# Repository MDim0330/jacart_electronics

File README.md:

**JACart Electronics Repo**

Contain Python and Arduino controller code for managing the Teleop board.

**Repo Contents**

cart_teleop_dac:/ Updated Arduino teleop code that utilizes DACs instead of PWM signals. This version should be the one used going forward.

python_teleop:/ Stand-alone python controller for teleop_board

libs:/ Require libraries for operating the Arudino teleop code

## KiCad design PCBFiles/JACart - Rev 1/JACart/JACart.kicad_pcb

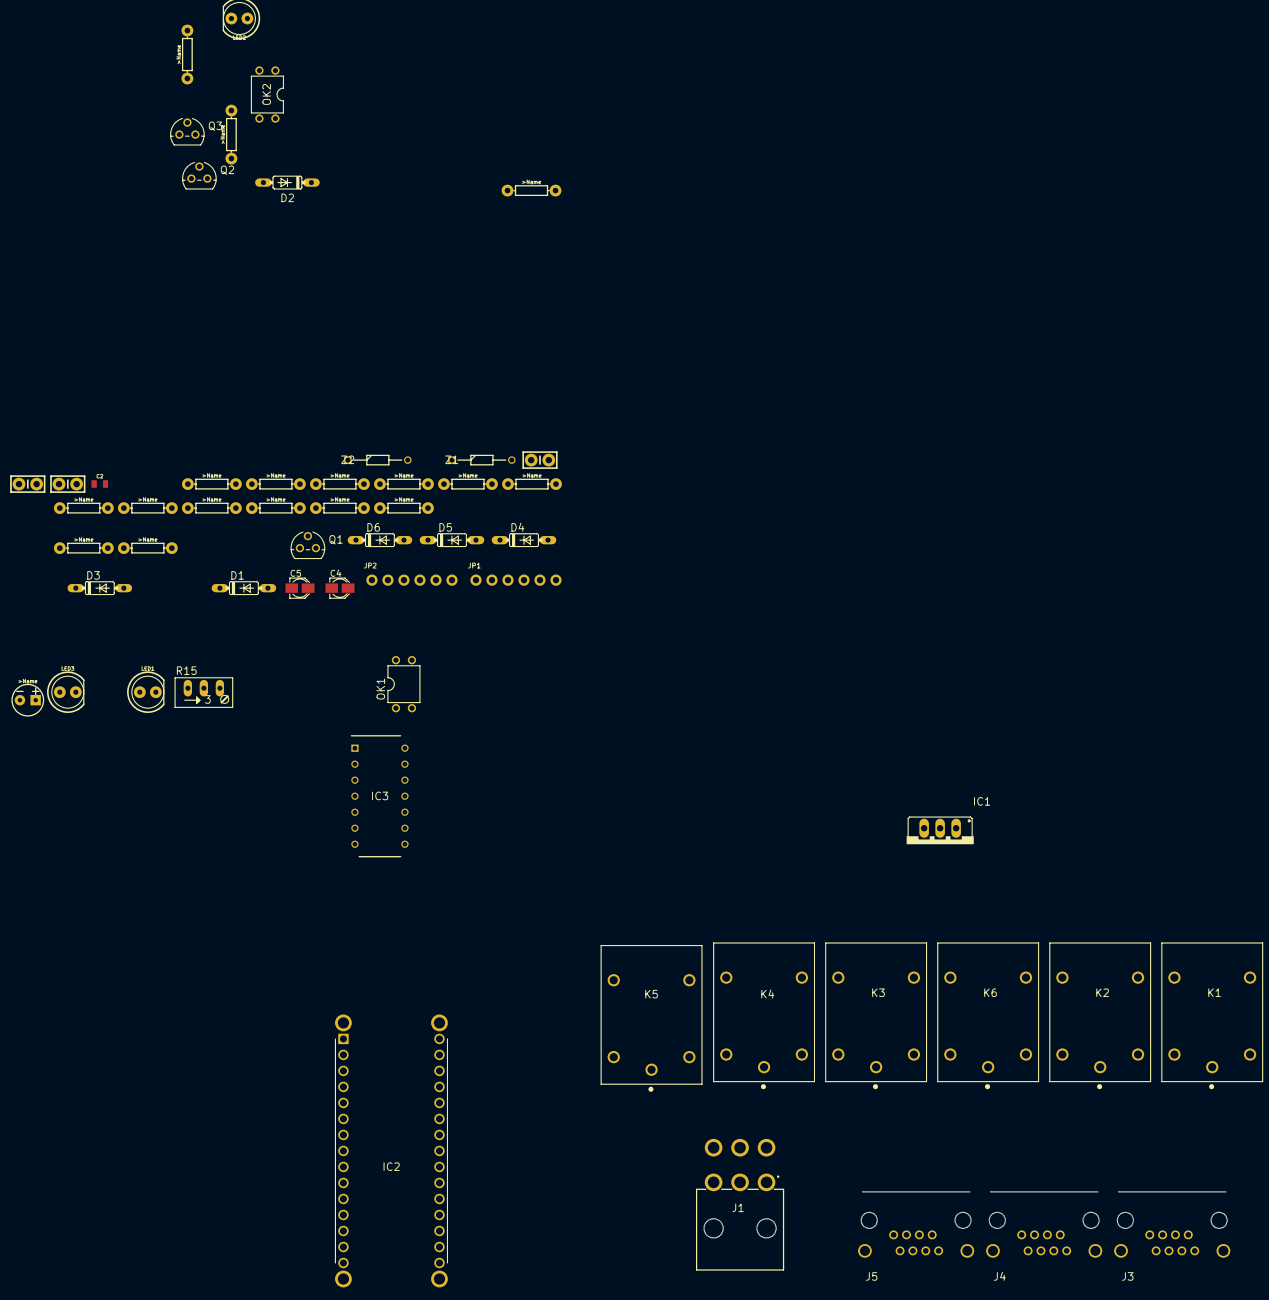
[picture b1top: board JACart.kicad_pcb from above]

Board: 2 copper layers, 56 parts (0 on the bottom side), 51 nets, no tracks yet.

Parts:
C1, C6: 0.1uF; CAP-PTH-SMALL-KIT
C2: 0.33µF; 0805
C3: 10uF; CPOL-RADIAL-2.5MM-5MM
C4, C5: 330uF; PANASONIC_A
C7: 1.0uF; CAP-PTH-SMALL-KIT
D1, D2, D3, D4, D5, D6: 1N4148; DO35-7
IC1: LM7805; 78XXS
IC2: ARD-NANO30NP; ARDNANO30NP
IC3: LMC6484IN; DIP794W56P254L1905H533Q14N
J1: 39-30-1060; 39-30-1060_1
J3: Steering; GLX-S-88M
J4: Brake; GLX-S-88M
J5: Throttle; GLX-S-88M
JP1, JP2: MCP4725; 1X06_ROUND_70
K1: Brake(1); RELAY_JS1-5V-F
K2: Brake(2); RELAY_JS1-5V-F
K3: Throttle(3); RELAY_JS1-5V-F
K4: Throttle(4); RELAY_JS1-5V-F
K5: Throttle; RELAY_JS1-5V-F
K6: Brake; RELAY_JS1-5V-F
LED1: Brake; LED_5MM
LED2: Throttle; LED_5MM
LED3: Auto; LED_5MM
OK1, OK2: PC817; DIL04
Q1, Q2, Q3: 2N3904; TO92
R1, R3: 510; AXIAL-0.3
R2, R4, R7, R9: 470; AXIAL-0.3
R5, R6, R13: 220; AXIAL-0.3
R8: 1M; AXIAL-0.3
R10: TBD; AXIAL-0.3
R11, R12, R14: 10k; AXIAL-0.3
R15: 1k; RJ9W
R16: 100; AXIAL-0.3
R17, R18: 1k; AXIAL-0.3
Z1, Z2: BAT85S-TR; DIOAD950W60L350D150

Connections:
5V: C1.1, C3.1, C6.1, D1.C, IC1.OUT, IC2.19, J1.2, J1.5, J3.2, JP1.1, JP2.1, JP2.5, K6.2, OK1.4
/AUTO: D3.C, D4.C, D5.C, D6.C, J1.3, K1.2, K2.2, K3.2, K4.2, R7.P$1
/BKA: IC2.11, R2.P$2
/BRKSIG: K1.3, Z1.1, Z2.1
/PANIC: IC3.4, J1.6, R14.P$2, R15.E, R18.P$2
/POTWPR: IC2.27, J3.1
/SCL: IC2.22, JP1.3, JP2.3
/SDA: IC2.23, JP1.4, JP2.4
/STRLFT: IC2.13, J3.8, JP2.6
/STRRT: IC2.12, J3.7, JP1.6
/TLA: IC2.10, R4.P$2
/TTLSIG: C4.+, K3.3, R5.P$1
GND: C1.2, C2.2, C3.2, C4.-, C5.-, C6.2, D3.A, D4.A, D5.A, D6.A, IC1.GND, IC2.4, IC2.17, IC3.11, J1.1, J3.3, J4.3, J5.3, JP1.2, JP2.2, K1.5, K2.5, K3.5, K4.5, LED1.K, LED2.K, LED3.K, Q1.3, Q2.3, Q3.3, R9.P$1, R13.P$1, R15.A
unnamed: C2.1, IC1.IN, J1.4
unnamed: C5.+, R6.P$1, Z1.2
unnamed: C7.1, IC3.7, Z2.2
unnamed: C7.2, R17.P$1
unnamed: D1.A, K6.5, Q1.1
unnamed: D2.A, K5.5, Q2.1
unnamed: D2.C, K5.2, OK2.4
unnamed: IC2.8, R5.P$2
unnamed: IC2.9, R6.P$2
unnamed: IC3.1, R8.P$2, R12.P$2
unnamed: IC3.2, R8.P$1, R11.P$1
unnamed: IC3.6, R10.P$1, R17.P$2
unnamed: IC3.12, R13.P$2, R14.P$1
unnamed: IC3.5, IC3.13, IC3.14, R16.P$1
unnamed: J4.2, K2.4
unnamed: J4.4, K1.4
unnamed: J4.6, K1.1
unnamed: J4.7, K6.1
unnamed: J4.8, K2.1
unnamed: J5.2, K4.4
unnamed: J5.4, K3.4
unnamed: J5.6, K3.1
unnamed: J5.7, K5.1
unnamed: J5.8, K4.1
unnamed: K2.3, K6.3
unnamed: K4.3, K5.3
unnamed: LED1.A, OK1.2
unnamed: LED2.A, OK2.2
unnamed: LED3.A, R7.P$2
unnamed: OK1.1, R2.P$1
unnamed: OK1.3, R1.P$2
unnamed: OK2.1, R4.P$1
unnamed: OK2.3, R3.P$2
unnamed: Q1.2, R1.P$1
unnamed: Q2.2, Q3.1, R3.P$1
unnamed: Q3.2, R18.P$1
unnamed: R9.P$2, R10.P$2, R12.P$1, R16.P$2
unnamed: R11.P$2, R15.S

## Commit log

2019-10-29 Add existing files
2019-11-19 v2.0
2020-06-03 commit of current arduino code
2020-08-19 fix binary format.
2020-08-19 remove some prints
2020-09-01 fix baud rate
2020-09-20 fix for python3
2020-09-20 improve reliability of serial reading
2020-09-20 fix bug
2020-10-18 add and rename teleop to this repo
2020-10-21 changed usb port to '/dev/ttyUSB9'
2020-11-05 Upload schematic of current controller board schematics
2020-11-11 new dac version
2020-11-12 Ignore my dev environment files
2020-11-12 Update comments
2020-11-12 Add libs folder to hold Arduino teleop libraries
2020-11-12 Deprecate old PWM teleop board
2020-11-17 Copy in Arduino libraries from local install
2020-11-24 Remove bad libraries folder
2020-11-24 Commenting and dead code removal
2020-11-24 Add requirements file to ensure correct packages are installed
2020-12-09 Add author tag
2021-01-21 Create install and run scripts for Python environment
2021-01-21 Add heartbeat and silence all prints
2021-01-21 Create PCBFiles
2021-01-21 Added Dick's PCB Files
    PCB Designs
2021-02-09 Add golf cart wiring diagrams
2021-03-08 Adding additional Eagle design files
2021-03-08 Add gitignore file
2021-03-08 Re-organize and delete hidden files
2021-03-29 Add in missing libs
2021-04-29 Resolve braking error and reduce verbosity
2021-05-06 Add abs() to ensure we avoid overflow errors
2021-06-01 Enable teleop to scan for correct port on MacOS
2021-06-02 Add diagnostic version
2021-06-15 Add Jorge documentation
2021-06-15 Clarify teleop comments
2021-06-16 Update chart schematics
2022-04-12 Add in missing Library
2022-05-12 updated PIDs for steering for Comm Circuit Board v1.0
2022-05-12 Added in CommBoardPCBFiles (new all-in-one board)
2022-06-15 Update cart_teleop_dac.ino
    KD value changed from 1.0 to 1.19
2022-06-16 New anolog port read and write
